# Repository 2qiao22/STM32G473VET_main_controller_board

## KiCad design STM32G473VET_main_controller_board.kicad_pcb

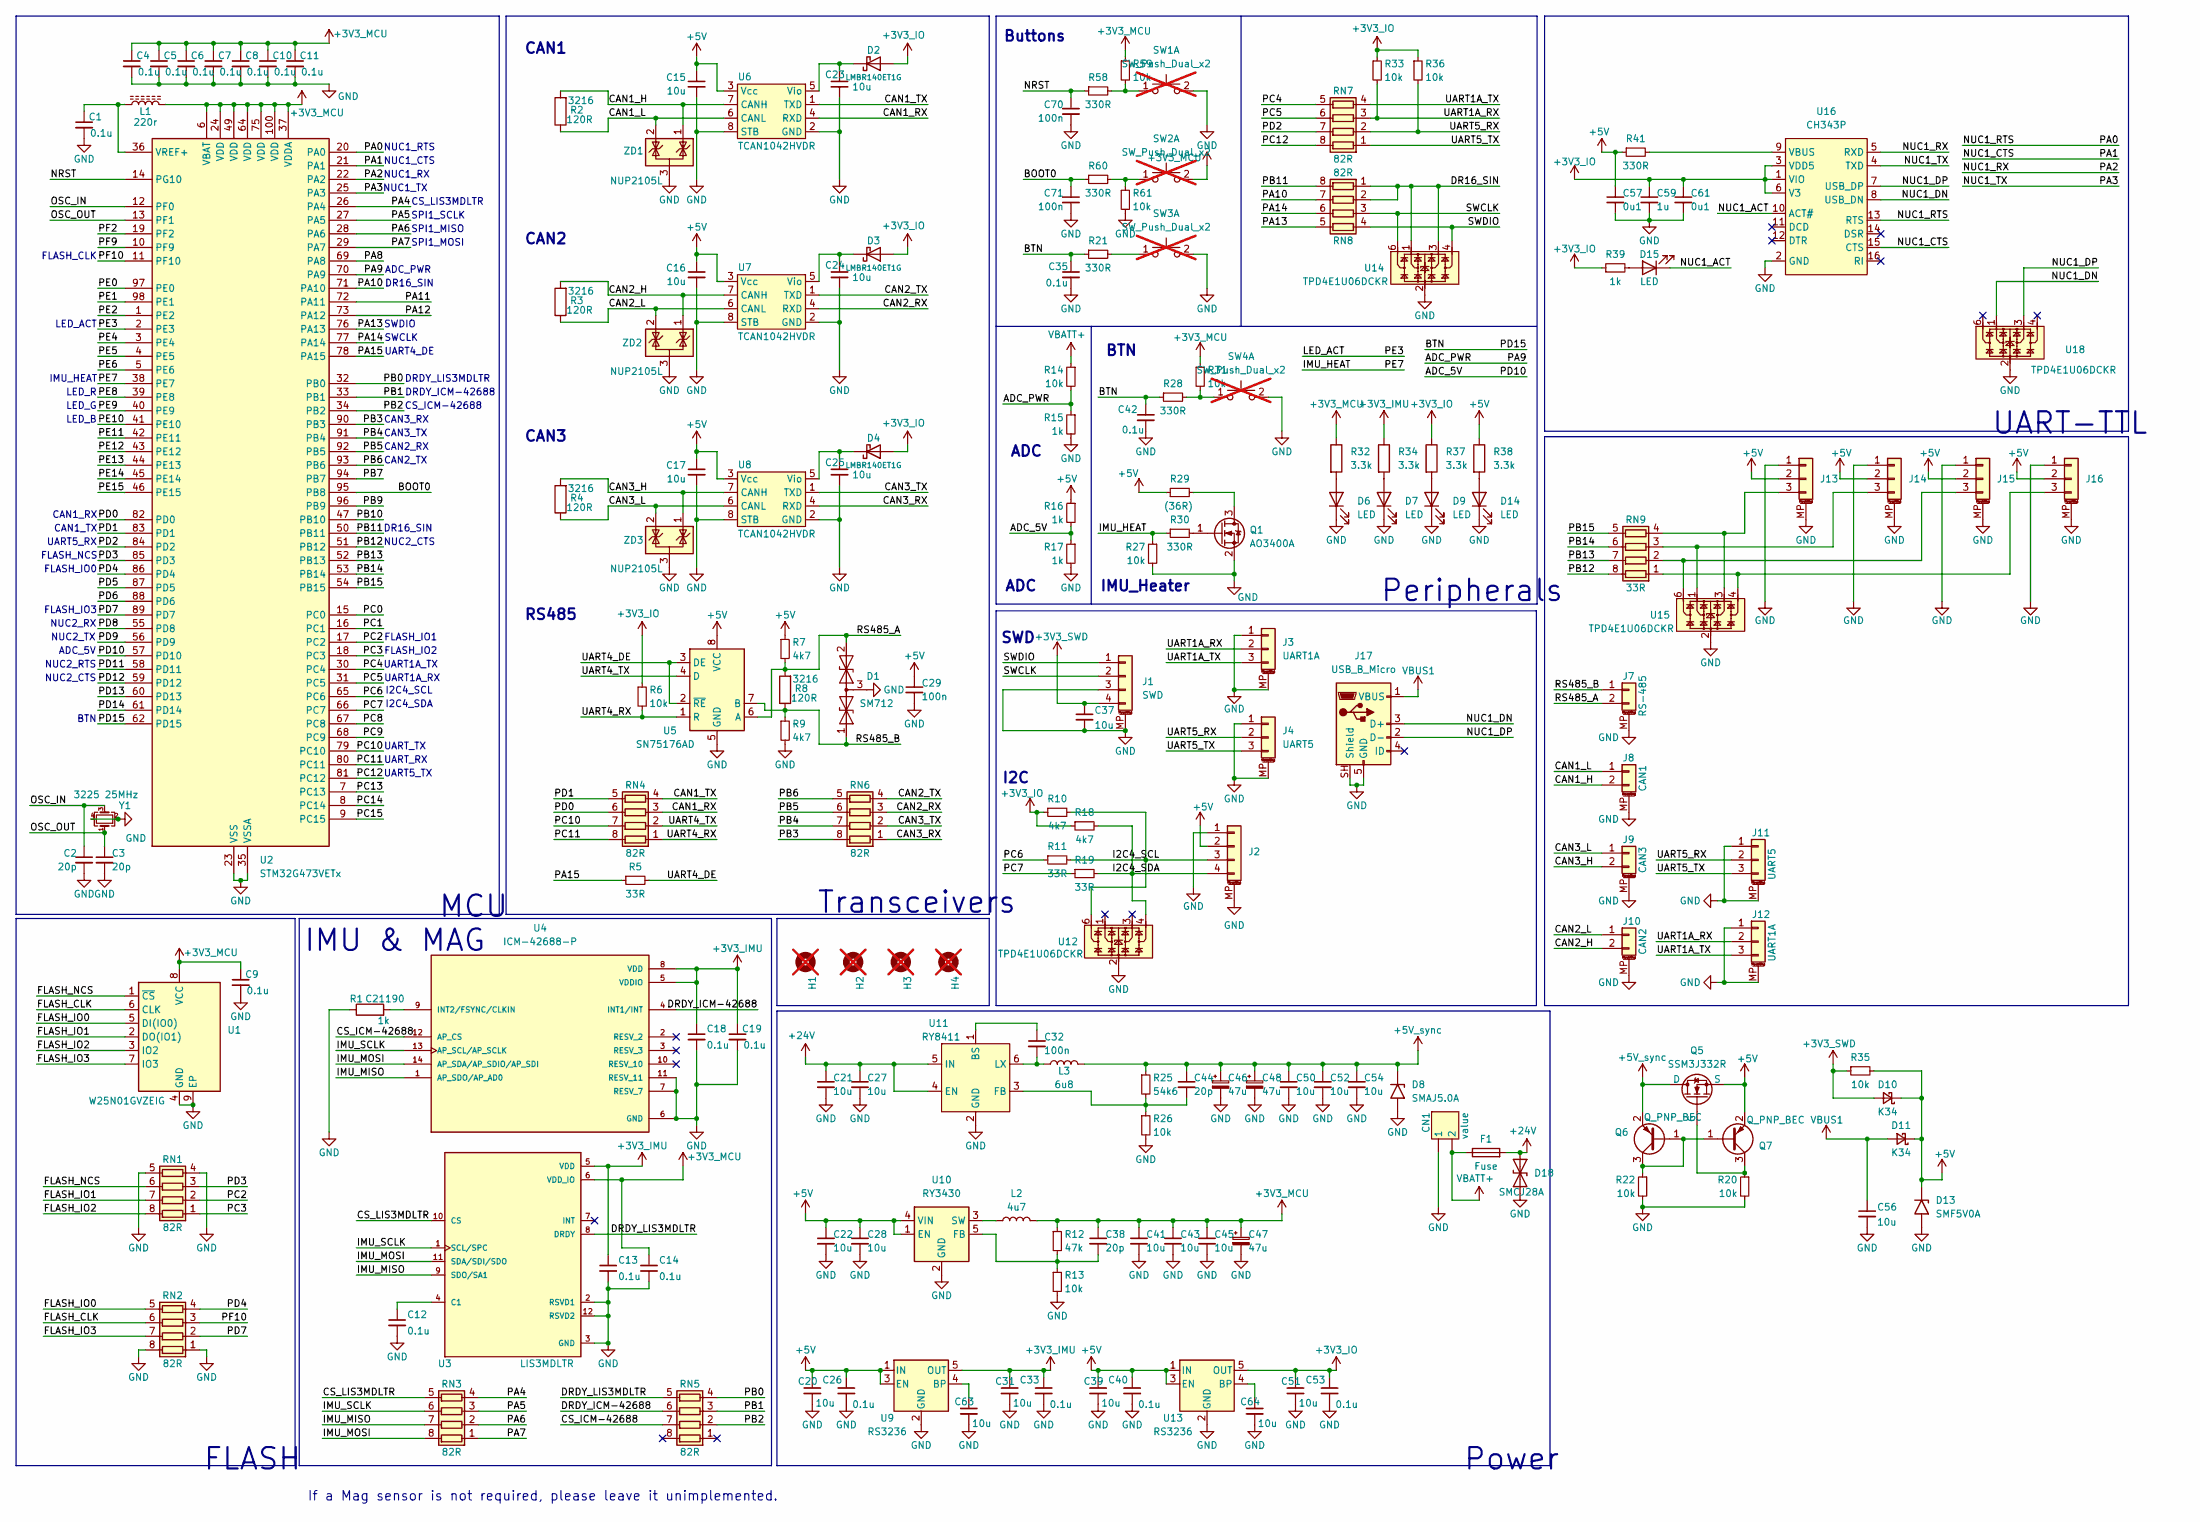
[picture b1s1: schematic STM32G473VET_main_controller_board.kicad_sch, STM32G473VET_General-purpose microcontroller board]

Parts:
C1, C4, C5, C6, C7, C8, C9, C10, C11, C12, C13, C14, C18, C19, C26, C33, C35, C40, C42, C53: 0.1u; C_0603_1608Metric; LCSC C14663
C2, C3, C38, C44: 20p; C_0603_1608Metric
C15, C16, C17, C20, C23, C24, C25, C31, C37, C39, C51, C56, C63, C64: 10u; C_1206_3216Metric; LCSC C13585
C21, C27, C50, C52, C54: 10u; C_1206_3216Metric
C22, C28, C41, C43, C45: 10u; C_0603_1608Metric
C29, C32, C70, C71: 100n; C_0603_1608Metric
C46, C47, C48: 47u; CP_EIA-3216-12_Kemet-S
C57, C61: 0u1; C_0603_1608Metric
C59: 1u; C_0603_1608Metric
CN1: value; AMASS_XT30PW-M_1x02_P2.50mm_Horizontal
D1: SM712; SOT-23
D2, D3, D4: LMBR140ET1G; D_TUMD2; LCSC C172430
D6, D7, D9, D14: LED; LED_0603_1608Metric; LCSC C510027
D8: SMAJ5.0A; D_SMA
D10, D11: K34; D_SMF
D13: SMF5V0A; D_SMF
D15: LED; LED_0603_1608Metric
D18: SMCJ28A; D_SMC
F1: Fuse; Fuse_1206_3216Metric
H1, H2, H3, H4: MountingHole; MountingHole_3.2mm_M3_ISO14580; not fitted
J1: SWD; Molex_PicoBlade_53398-0471_1x04-1MP_P1.25mm_Vertical
J2: Conn_01x04_MountingPin; 128x64OLED
J3: UART1A; JST_GH_BM03B-GHS-TBT_1x03-1MP_P1.25mm_Vertical
J4: UART5; JST_GH_BM03B-GHS-TBT_1x03-1MP_P1.25mm_Vertical
J7: RS-485; JST_GH_SM02B-GHS-TB_1x02-1MP_P1.25mm_Horizontal
J8: CAN1; JST_GH_SM02B-GHS-TB_1x02-1MP_P1.25mm_Horizontal
J9: CAN3; JST_GH_SM02B-GHS-TB_1x02-1MP_P1.25mm_Horizontal
J10: CAN2; JST_GH_SM02B-GHS-TB_1x02-1MP_P1.25mm_Horizontal
J11: UART5; JST_GH_SM03B-GHS-TB_1x03-1MP_P1.25mm_Horizontal
J12: UART1A; JST_GH_SM03B-GHS-TB_1x03-1MP_P1.25mm_Horizontal
J13, J14, J15, J16: Conn_01x03_MountingPin; JST_GH_BM03B-GHS-TBT_1x03-1MP_P1.25mm_Vertical
J17: USB_B_Micro; USB_Micro-B_Wuerth_629105150521
L1: 220r; L_0603_1608Metric
L2: 4u7; L_Sunlord_MWSA0402S
L3: 6u8; L_Sunlord_MWSA0402S
Q1: AO3400A; SOT-23
Q5: SSM3J332R; SOT-23-3
Q6, Q7: Q_PNP_BEC; SOT-23-3
R1: 1k; R_0603_1608Metric; LCSC C21190
R2, R3, R4, R8: 120R; R_1206_3216Metric; LCSC C17909
R5, R11, R19: 33R; R_0603_1608Metric
R6, R13, R14, R20, R22, R26, R27, R31, R33, R35, R36, R59, R61: 10k; R_0603_1608Metric
R7, R9, R10, R18: 4k7; R_0603_1608Metric
R12: 47k; R_0603_1608Metric
R15, R16, R17, R39: 1k; R_0603_1608Metric
R21, R28, R30, R41, R58, R60: 330R; R_0603_1608Metric
R25: 54k6; R_0603_1608Metric
R29: (36R); R_1206_3216Metric
R32, R34, R37, R38: 3.3k; R_0603_1608Metric; LCSC C4109
RN1, RN2, RN3, RN4, RN5, RN6, RN7, RN8: 82R; R_Array_Concave_4x0603
RN9: 33R; R_Array_Concave_4x0603
SW1, SW2, SW3, SW4: SW_Push_Dual_x2; SW_Push_TVAF06; not fitted
U1: W25N01GVZEIG; WSON-8-1EP_8x6mm_P1.27mm_EP3.4x4.3mm
U2: STM32G473VETx; LQFP-100_14x14mm_P0.5mm
U3: LIS3MDLTR; XDCR_LIS3MDLTR; PARTREV 6
U4: ICM-42688-P; PQFN50P300X250X97-14N; PARTREV 1.2; LCSC C48586483
U5: SN75176AD; SOIC-8_3.9x4.9mm_P1.27mm
U6, U7, U8: TCAN1042HVDR; SOIC-8_3.9x4.9mm_P1.27mm; LCSC C485807
U9, U13: RS3236; SOT-23-5
U10: RY3430; SOT-23-5
U11: RY8411; SOT-23-6
U12, U14, U15, U18: TPD4E1U06DCKR; SOT-363_SC-70-6
U16: CH343P; TQFN-16-1EP_3x3mm_P0.5mm_EP1.6x1.6mm
Y1: 3225 25MHz; Crystal_SMD_3225-4Pin_3.2x2.5mm
ZD1, ZD2, ZD3: NUP2105L; SOT-23; LCSC C14486

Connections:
+3V3_IMU: C13.1, C18.1, C19.1, C31.1, C33.1, R34.1, U3.5 (VDD), U4.5 (VDDIO), U4.8 (VDD), U9.5 (OUT)
+3V3_IO: C51.1, C53.1, C59.1, C61.1, D2.2 (A), D3.2 (A), D4.2 (A), R6.1, R10.1, R18.1, R33.1, R36.1, R37.1, R39.1, U13.5 (OUT), U16.1 (VIO), U16.3 (VDD5), U16.6 (V3)
+3V3_MCU: C4.1, C5.1, C6.1, C7.1, C8.1, C9.1, C10.1, C11.1, C14.1, C38.1, C41.1, C43.1, C45.1, C47.1, L1.2, L2.2, R12.1, R31.1, R32.1, R59.1, SW2.2 (D), U1.8 (VCC), U2.6 (VBAT), U2.24 (VDD), U2.37 (VDDA), U2.49 (VDD), U2.64 (VDD), U2.75 (VDD), U2.100 (VDD), U3.6 (VDD_IO); also elsewhere on the board
+3V3_SWD: C37.1, D10.2 (A), J1.4, R35.1
+5V: C15.1, C16.1, C17.1, C20.1, C22.1, C26.1, C28.1, C29.1, C39.1, C40.1, C57.1, D10.1 (K), D11.1 (K), D13.1 (A1), J2.2, J13.2, J14.2, J15.2, J16.2, Q5.3 (S), Q7.2 (E), R7.1, R16.1, R29.1, R35.2, R38.1, R41.1, U5.8 (VCC), U6.3 (Vcc), U7.3 (Vcc), U8.3 (Vcc), U9.1 (IN), U9.3 (EN), U10.1 (EN), U10.4 (VIN), U13.1 (IN), U13.3 (EN)
+5V_sync: C44.1, C46.1, C48.1, C50.1, C52.1, C54.1, D8.1 (A1), L3.2, Q5.1 (D), Q6.2 (E), R25.1
+24V: C21.1, C27.1, D18.1 (A1), F1.2, U11.4 (EN), U11.5 (IN)
/ADC_5V: R16.2, R17.1, U2.57 (PD10)
/ADC_PWR: R14.2, R15.1, U2.70 (PA9)
/BOOT0: C71.1, R60.1, U2.95 (PB8)
/BTN: C35.1, C42.1, R21.1, R28.1, U2.62 (PD15)
/CAN1_H: J8.2, R2.2, U6.7 (CANH), ZD1.1 (K)
/CAN1_L: J8.1, R2.1, U6.6 (CANL), ZD1.2 (K)
/CAN1_RX: RN4.3 (R3.1), U6.4 (RXD)
/CAN1_TX: RN4.4 (R4.1), U6.1 (TXD)
/CAN2_H: J10.2, R3.2, U7.7 (CANH), ZD2.1 (K)
/CAN2_L: J10.1, R3.1, U7.6 (CANL), ZD2.2 (K)
/CAN2_RX: RN6.3 (R3.1), U7.4 (RXD)
/CAN2_TX: RN6.4 (R4.1), U7.1 (TXD)
/CAN3_H: J9.2, R4.2, U8.7 (CANH), ZD3.1 (K)
/CAN3_L: J9.1, R4.1, U8.6 (CANL), ZD3.2 (K)
/CAN3_RX: RN6.1 (R1.1), U8.4 (RXD)
/CAN3_TX: RN6.2 (R2.1), U8.1 (TXD)
/CS_ICM-42688: RN5.7 (R2.2), U4.12 (AP_CS)
/CS_LIS3MDLTR: RN3.5 (R4.2), U3.10 (CS)
/DR16_SIN: RN8.1 (R1.1), RN8.2 (R2.1), U14.1, U14.3
/DRDY_ICM-42688: RN5.6 (R3.2), U4.4 (INT1/INT)
/DRDY_LIS3MDLTR: RN5.5 (R4.2), U3.8 (DRDY)
/FLASH_CLK: RN2.6 (R3.2), U1.6 (CLK)
/FLASH_IO0: RN2.5 (R4.2), U1.5 (DI(IO0))
/FLASH_IO1: RN1.7 (R2.2), U1.2 (DO(IO1))
/FLASH_IO2: RN1.8 (R1.2), U1.3 (IO2)
/FLASH_IO3: RN2.7 (R2.2), U1.7 (IO3)
/FLASH_NCS: RN1.6 (R3.2), U1.1 (~CS)
/I2C4_SCL: J2.3, R10.2, R11.2, U12.6
/I2C4_SDA: J2.4, R18.2, R19.2, U12.4
/IMU_HEAT: R27.1, R30.1, U2.38 (PE7)
/IMU_MISO: RN3.7 (R2.2), U3.9 (SDO/SA1), U4.1 (AP_SDO/AP_AD0)
/IMU_MOSI: RN3.8 (R1.2), U3.11 (SDA/SDI/SDO), U4.14 (AP_SDA/AP_SDIO/AP_SDI)
/IMU_SCLK: RN3.6 (R3.2), U3.1 (SCL/SPC), U4.13 (AP_SCL/AP_SCLK)
/LED_ACT: U2.2 (PE3)
/NRST: C70.1, R58.1, U2.14 (PG10)
/NUC1_ACT: D15.1 (K), U16.10 (ACT#)
/NUC1_CTS: U2.21 (PA1), U16.15 (CTS)
/NUC1_DN: J17.3 (D+), U16.8 (USB_DN), U18.1
/NUC1_DP: J17.2 (D-), U16.7 (USB_DP), U18.3
/NUC1_RTS: U2.20 (PA0), U16.13 (RTS)
/NUC1_RX: U2.22 (PA2), U16.5 (RXD)
/NUC1_TX: U2.25 (PA3), U16.4 (TXD)
/OSC_IN: C2.1, U2.12 (PF0), Y1.3
/OSC_OUT: C3.1, U2.13 (PF1), Y1.1
/PA4: RN3.4 (R4.1), U2.26 (PA4)
/PA5: RN3.3 (R3.1), U2.27 (PA5)
/PA6: RN3.2 (R2.1), U2.28 (PA6)
/PA7: RN3.1 (R1.1), U2.29 (PA7)
/PA8: U2.69 (PA8)
/PA10: RN8.7 (R2.2), U2.71 (PA10)
/PA11: U2.72 (PA11)
/PA12: U2.73 (PA12)
/PA13: RN8.5 (R4.2), U2.76 (PA13)
/PA14: RN8.6 (R3.2), U2.77 (PA14)
/PA15: R5.1, U2.78 (PA15)
/PB0: RN5.4 (R4.1), U2.32 (PB0)
/PB1: RN5.3 (R3.1), U2.33 (PB1)
/PB2: RN5.2 (R2.1), U2.34 (PB2)
/PB3: RN6.8 (R1.2), U2.90 (PB3)
/PB4: RN6.7 (R2.2), U2.91 (PB4)
/PB5: RN6.6 (R3.2), U2.92 (PB5)
/PB6: RN6.5 (R4.2), U2.93 (PB6)
/PB7: U2.94 (PB7)
/PB9: U2.96 (PB9)
/PB10: U2.47 (PB10)
/PB11: RN8.8 (R1.2), U2.50 (PB11)
/PB12: RN9.8 (R1.2), U2.51 (PB12)
/PB13: RN9.7 (R2.2), U2.52 (PB13)
/PB14: RN9.6 (R3.2), U2.53 (PB14)
/PB15: RN9.5 (R4.2), U2.54 (PB15)
/PC0: U2.15 (PC0)
/PC1: U2.16 (PC1)
/PC2: RN1.2 (R2.1), U2.17 (PC2)
/PC3: RN1.1 (R1.1), U2.18 (PC3)
/PC4: RN7.5 (R4.2), U2.30 (PC4)
/PC5: RN7.6 (R3.2), U2.31 (PC5)
/PC6: R11.1, U2.65 (PC6)
/PC7: R19.1, U2.66 (PC7)
/PC8: U2.67 (PC8)
/PC9: U2.68 (PC9)
/PC10: RN4.7 (R2.2), U2.79 (PC10)
/PC11: RN4.8 (R1.2), U2.80 (PC11)
/PC12: RN7.8 (R1.2), U2.81 (PC12)
/PC13: U2.7 (PC13)
/PC14: U2.8 (PC14)
/PC15: U2.9 (PC15)
/PD0: RN4.6 (R3.2), U2.82 (PD0)
/PD1: RN4.5 (R4.2), U2.83 (PD1)
/PD2: RN7.7 (R2.2), U2.84 (PD2)
/PD3: RN1.3 (R3.1), U2.85 (PD3)
/PD4: RN2.4 (R4.1), U2.86 (PD4)
/PD5: U2.87 (PD5)
/PD6: U2.88 (PD6)
/PD7: RN2.2 (R2.1), U2.89 (PD7)
/PD8: U2.55 (PD8)
/PD9: U2.56 (PD9)
/PD11: U2.58 (PD11)
/PD12: U2.59 (PD12)
/PD13: U2.60 (PD13)
/PD14: U2.61 (PD14)
/PE0: U2.97 (PE0)
/PE1: U2.98 (PE1)
/PE2: U2.1 (PE2)
/PE4: U2.3 (PE4)
/PE5: U2.4 (PE5)
/PE6: U2.5 (PE6)
/PE8: U2.39 (PE8)
/PE9: U2.40 (PE9)
/PE10: U2.41 (PE10)
/PE11: U2.42 (PE11)
/PE12: U2.43 (PE12)
/PE13: U2.44 (PE13)
/PE14: U2.45 (PE14)
/PE15: U2.46 (PE15)
/PF2: U2.19 (PF2)
/PF9: U2.10 (PF9)
/PF10: RN2.3 (R3.1), U2.11 (PF10)
/RS485_A: D1.2 (A2), J7.2, R7.2, R8.2, U5.6 (A)
/RS485_B: D1.1 (A1), J7.1, R8.1, R9.1, U5.7 (B)
/SWCLK: J1.2, RN8.3 (R3.1), U14.6
/SWDIO: J1.1, RN8.4 (R4.1), U14.4
/UART1A_RX: J3.2, J12.2, R33.2, RN7.3 (R3.1)
/UART1A_TX: J3.3, J12.3, RN7.4 (R4.1)
/UART4_DE: R5.2, U5.2 (~RE), U5.3 (DE)
/UART4_RX: R6.2, RN4.1 (R1.1), U5.1 (R)
/UART4_TX: RN4.2 (R2.1), U5.4 (D)
/UART5_RX: J4.2, J11.2, R36.2, RN7.2 (R2.1)
/UART5_TX: J4.3, J11.3, RN7.1 (R1.1)
GND: C1.2, C2.2, C3.2, C4.2, C5.2, C6.2, C7.2, C8.2, C9.2, C10.2, C11.2, C12.2, C13.2, C14.2, C15.2, C16.2, C17.2, C18.2, C19.2, C20.2, C21.2, C22.2, C23.2, C24.2, C25.2, C26.2, C27.2, C28.2, C29.2, C31.2, C33.2, C35.2, C37.2, C39.2, C40.2, C41.2, C42.2, C43.2, C45.2, C46.2, C47.2, C48.2, C50.2, C51.2, C52.2, C53.2, C54.2, C56.2, C57.2, C59.2, C61.2, C63.2, C64.2, C70.2, C71.2, CN1.1, D1.3 (common), D6.1 (K), D7.1 (K), D8.2 (A2), D9.1 (K), D13.2 (A2), D14.1 (K), D18.2 (A2), J1.3, J1.MP (MountPin), J2.1, J2.MP (MountPin), J3.1, J3.MP (MountPin), J4.1, J4.MP (MountPin), J7.MP (MountPin), J8.MP (MountPin), J9.MP (MountPin), J10.MP (MountPin), J11.1, J11.MP (MountPin), J12.1, J12.MP (MountPin), J13.1, J13.MP (MountPin), J14.1, J14.MP (MountPin), J15.1, J15.MP (MountPin), J16.1, J16.MP (MountPin), J17.5 (GND), J17.SH (Shield), Q1.2 (S), R1.1, R9.2, R13.2, R15.2, R17.2, R20.2, R22.2, R26.2, R27.2, R61.2, RN1.4 (R4.1), RN1.5 (R4.2), RN2.1 (R1.1), RN2.8 (R1.2), SW1.2 (D), SW3.2 (D), SW4.2 (D), U1.4 (GND), U1.9 (EP), U2.23 (VSS), U2.35 (VSSA), U2.48 (VSS), U2.63 (VSS), U2.74 (VSS), U2.99 (VSS), U3.2 (RSVD1), U3.3 (GND), U3.12 (RSVD2), U4.6 (GND), U4.7 (RESV_7), U4.11 (RESV_11), U5.5 (GND), U6.2 (GND), U6.8 (STB), U7.2 (GND), U7.8 (STB), U8.2 (GND), U8.8 (STB), U9.2 (GND), U10.2 (GND), U11.2 (GND), U12.2, U13.2 (GND), U14.2, U15.2, U16.2 (GND), U16.17 (GND), U18.2, Y1.2, Y1.4, ZD1.3 (A), ZD2.3 (A), ZD3.3 (A)
unnamed: C23.1, D2.1 (K), U6.5 (Vio)
unnamed: C24.1, D3.1 (K), U7.5 (Vio)
unnamed: C25.1, D4.1 (K), U8.5 (Vio)
unnamed: D6.2 (A), R32.2
unnamed: D7.2 (A), R34.2
unnamed: D9.2 (A), R37.2
unnamed: D14.2 (A), R38.2
unnamed: D15.2 (A), R39.2
unnamed: J13.3, RN9.4 (R4.1), U15.3
unnamed: J14.3, RN9.3 (R3.1), U15.1
unnamed: J15.3, RN9.2 (R2.1), U15.6
unnamed: J16.3, RN9.1 (R1.1), U15.4
unnamed: Q1.3 (D), R29.2
unnamed: Q1.1 (G), R30.2
unnamed: Q5.2 (G), Q7.3 (C), R20.1
unnamed: Q6.1 (B), Q6.3 (C), Q7.1 (B), R22.1
unnamed: R58.2, R59.2, SW1.1 (C)
unnamed: R60.2, R61.1, SW2.1 (C)
unnamed: R21.2, SW3.1 (C)
unnamed: R28.2, R31.2, SW4.1 (C)
unnamed: C1.1, L1.1, U2.36 (VREF+)
unnamed: C12.1, U3.4 (C1)
unnamed: R1.2, U4.9 (INT2/FSYNC/CLKIN)
unnamed: C63.1, U9.4 (BP)
unnamed: C38.2, R12.2, R13.1, U10.5 (FB)
unnamed: L2.1, U10.3 (SW)
unnamed: C32.1, U11.1 (BS)
unnamed: C44.2, R25.2, R26.1, U11.3 (FB)
unnamed: C32.2, L3.1, U11.6 (LX)
unnamed: C64.1, U13.4 (BP)
unnamed: R41.2, U16.9 (VBUS)
VBATT+: CN1.2, F1.1, R14.1
VBUS1: C56.1, D11.2 (A), J17.1 (VBUS)

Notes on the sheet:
CS_LIS3MDLTR
LED_ACT
ADC_5V
SWCLK
NUC2_TX
NUC2_CTS
SWD
LED_B
CAN2_RX
NUC1_CTS
BTN
I2C4_SDA
FLASH
FLASH_IO3
UART_TX
SPI1_MOSI
UART5_RX
MCU
NUC1_RTS
CAN3_TX
IMU & MAG
ADC
Buttons
CAN3
UART-TTL
NUC2_RX
UART5_TX
UART_RX
CAN1_TX
UART1A_RX
NUC2_RTS
FLASH_NCS
FLASH_IO0
If a Mag sensor is not required, please leave it unimplemented.
Peripherals
UART4_DE
Transceivers
ADC_PWR
UART1A_TX
CAN3_RX

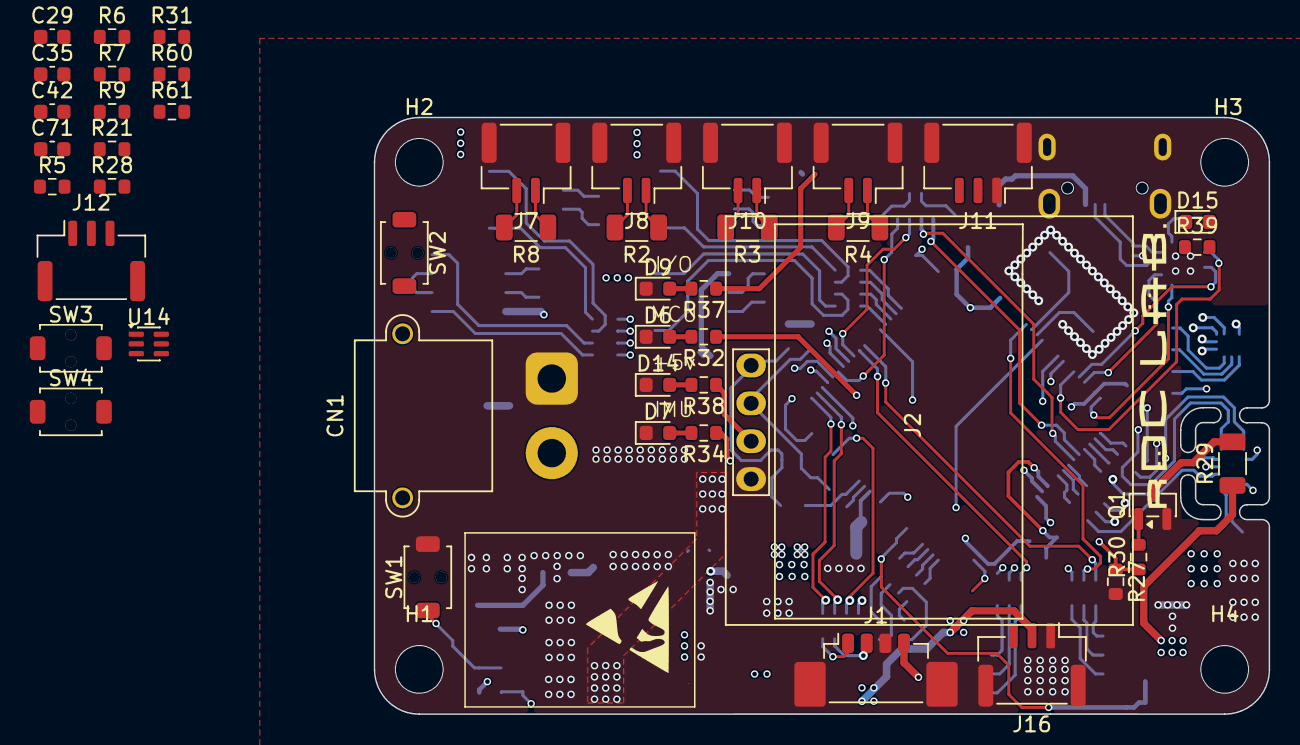
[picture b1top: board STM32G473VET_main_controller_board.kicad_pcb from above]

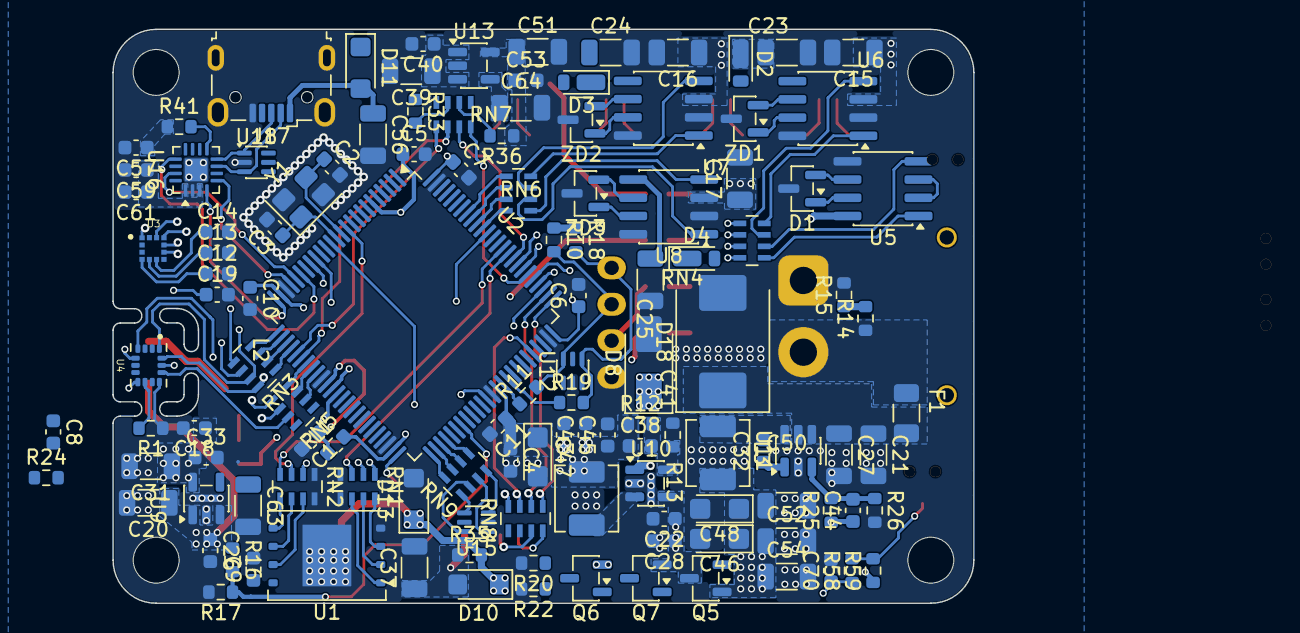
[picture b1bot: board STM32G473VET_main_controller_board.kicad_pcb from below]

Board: 4 copper layers, 60.0 x 40.0 mm, 172 parts (122 on the bottom side), 131 nets.

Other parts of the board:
R24: 10k; R_0603_1608Metric

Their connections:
+3V3_MCU: R24.1; also elsewhere on the board
